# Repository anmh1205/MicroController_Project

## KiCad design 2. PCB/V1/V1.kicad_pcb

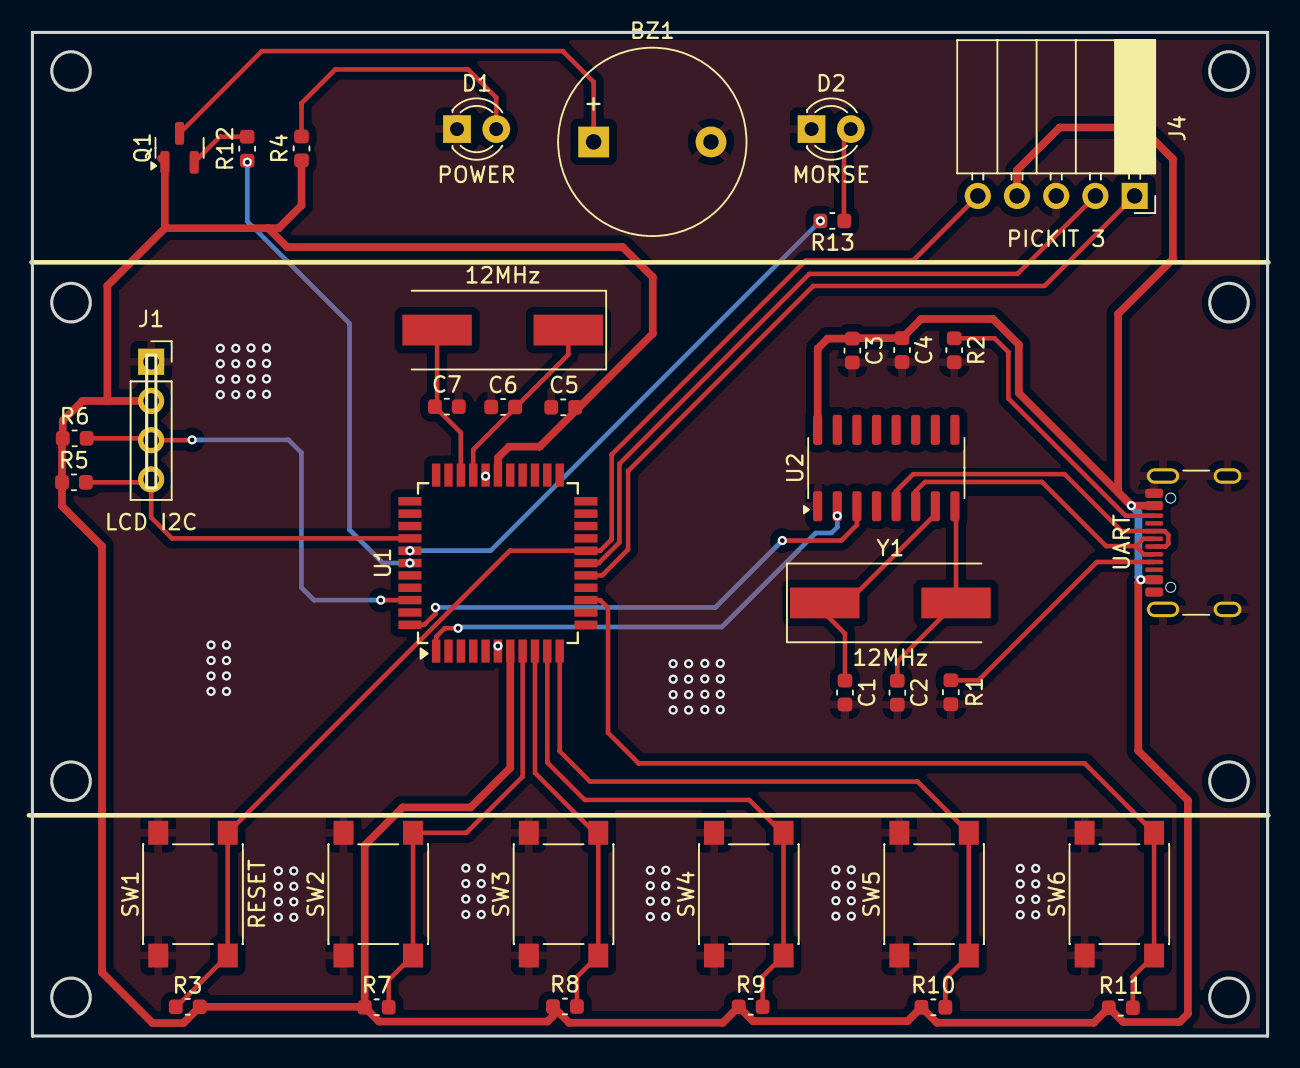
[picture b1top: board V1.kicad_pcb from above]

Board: 2 copper layers, 80.0 x 65.0 mm, 37 parts (0 on the bottom side), 28 nets.

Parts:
BZ1: Buzzer; Buzzer_12x9.5RM7.6
C1, C2, C6, C7: 22p; C_0603_1608Metric
C3: 10uF; C_0603_1608Metric
C4: 100nF; C_0603_1608Metric
C5: 100n; C_0603_1608Metric
D1: POWER; LED_D3.0mm
D2: MORSE; LED_D3.0mm
J1: LCD I2C; PinSocket_1x04_P2.54mm_Vertical
J2: USB_C_Receptacle_USB2.0_16P; USB_C_Receptacle_GCT_USB4105-xx-A_16P_TopMnt_Horizontal
J4: Conn_01x05_Socket; PinSocket_1x05_P2.54mm_Horizontal
Q1: S8550; SOT-23
R1, R2: 5.1K; C_0603_1608Metric
R3: 10k; C_0603_1608Metric
R4, R13: 330; C_0603_1608Metric
R5, R6: 4.7k; C_0603_1608Metric
R7, R8, R9, R10, R11: 10K; C_0603_1608Metric
R12: 1K; C_0603_1608Metric
SW1: RESET; SW_Push_1P1T_NO_6x6mm_H9.5mm
SW2, SW3, SW4, SW5, SW6: SW_Push; SW_Push_1P1T_NO_6x6mm_H9.5mm
U1: PIC16F887-I_PT; TQFP-44_10x10mm_P0.8mm
U2: CH340G; SOIC-16_3.9x9.9mm_P1.27mm
Y1, Y2: 12MHz; Crystal_SMD_HC49-SD

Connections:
+5V: C3.1, C4.1, C5.1, J1.2, J2.A4 (VBUS), J2.A9 (VBUS), J2.B4 (VBUS), J2.B9 (VBUS), J4.4, Q1.1 (E), R3.1, R4.1, R5.1, R6.1, R7.1, R8.1, R9.1, R10.1, R11.1, U1.7 (VDD), U1.28 (VDD_2), U2.16 (VCC)
/BUZZER: R12.1, U1.39 (RD1)
/CLK: J4.1, U1.16 (RB6/ICSPCLK)
/D+: J2.A6 (D+), J2.B6 (D+), U2.5 (UD+)
/D-: J2.A7 (D-), J2.B7 (D-), U2.6 (UD-)
/DAT: J4.2, U1.17 (RB7/ICSPDAT)
/LED: R13.1, U1.38 (RD0)
/RXD: U1.44 (RC6/TX/CK), U2.3 (RXD)
/SCL: J1.4, R5.2, U1.37 (RC3/SCK/SCL)
/SDA: J1.3, R6.2, U1.42 (RC4/SDI/SDA)
/SW0: R7.2, SW2.2, U1.8 (RB0/AN12/INT)
/SW1: R8.2, SW3.2, U1.9 (RB1/AN10/C12IN3-)
/SW2: R9.2, SW4.2, U1.10 (RB2/AN8)
/SW3: R10.2, SW5.2, U1.11 (RB3/AN9/PGM/C12IN2-)
/SW4: R11.2, SW6.2, U1.14 (RB4/AN11)
/TXD: U1.1 (RC7/RX/DT), U2.2 (TXD)
/Vpp: J4.5, R3.2, SW1.2, U1.18 (RE3/~MCLR/VPP)
GND: BZ1.2 (+), C1.2, C2.2, C3.2, C4.2, C5.2, C6.2, C7.2, D1.1 (K), D2.1 (K), J1.1, J2.A1 (GND), J2.A12 (GND), J2.B1 (GND), J2.B12 (GND), J2.S1 (SHIELD), J4.3, R1.1, R2.2, SW1.1, SW2.1, SW3.1, SW4.1, SW5.1, SW6.1, U1.6 (VSS_2), U1.29 (VSS), U2.1 (GND)
unnamed: BZ1.1 (-), Q1.3 (C)
unnamed: D1.2 (A), R4.2
unnamed: D2.2 (A), R13.2
unnamed: J2.A5 (CC1), R1.2
unnamed: J2.B5 (CC2), R2.1
unnamed: Q1.2 (B), R12.2
unnamed: C7.1, U1.31 (RA6/OSC2/CLKOUT), Y2.2
unnamed: C6.1, U1.30 (RA7/OSC1/CLKIN), Y2.1
unnamed: C1.1, U2.7 (XI), Y1.1
unnamed: C2.1, U2.8 (XO), Y1.2

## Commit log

2024-07-02 init commit
2024-07-04 completed pcd and lcd_i2c lib
2024-07-05 completed prototype code
2024-07-05 completed (V1.2)
2024-07-06 - completed morseCodeReader.c and morseCodeSpeaker.c - completed BUTTON_MODE
2024-07-06 - completed UART input mode - clearAll issue
2024-07-07 - completed UART Mode
2024-07-07 update pcb
2024-07-08 done flow chart
2024-07-16 up to date Document
2024-07-21 update document
2024-07-27 edit timer 16MHz => 12MHz
2024-08-07 update (07/08/2024)
